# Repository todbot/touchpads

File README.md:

# Touchpads and Touchwheels

Some capacitive sense touch sensors: buttons and touchwheels

Design your own sliders and wheels with the
[Captouch Designer](https://todbot.github.io/touchpads/captouch-designer/)
web app (source in [`captouch-designer/`](./captouch-designer/)).

## Touchpads

Touchpads are capacitive sensing button inputs that consist of a copper
pad and (usually) 1M pull-down resistor, both hooked up to a microcontroller GPIO pin.
Code on a microcontroller repeatedly charges and times the discharge rate of the pad.
The discharge time changes when a finger is close to the pad. 
This change can be used to detect a button press. 
The CircuitPython [`touchio`](https://circuitpython-github-jepler.readthedocs.io/en/latest/shared-bindings/touchio/index.html) library and the Arduino library [`TouchyTouch`](https://github.com/todbot/TouchyTouch)
are two ways of using these capacative touch pads

### Touchpad boards

* buttons4x0 - Four 11 mm capacitive touch buttons for use with breadboards or in a project
  
  https://github.com/user-attachments/assets/d40d3ede-4ee4-4309-8d3a-04f324b11f05

## Touchwheels

These work by using only three capactive touch pads in a specific interleaved 
geometry and measuring the relative ratio of analog capacitive touch values 
between the pads to compute a distance along the slider. 

### Touchwheel boards made so far:

* TouchWheelSAO -- [Touchwheel SAO as part of  Hackaday Supercon 2024 badge](https://github.com/todbot/TouchwheelSAO)

* touchwheel0 - [available on Tindie as a kit!](https://www.tindie.com/products/todbot/touchwheel0-capacitive-touch-wheel/)

  Similar to an iPod's wheel, `touchwheel0` is a 30 mm (0.6") diameter 
  [rotary capacitive touch slider](https://onlinedocs.microchip.com/pr/GUID-A8A0085D-58D1-4E41-A07D-B93BFDE11AFE-en-US-4/index.html?GUID-FB5E9311-C731-4326-82D2-CD5F0ED8E378) that can be used with most any microcontroller. It uses three digital GPIO pins and requires no extra components. The included examples in CircuitPython and Arduino show how to turn the raw capacitive touch readings of the three pins into a linear 0-360º angle measurement.

* picoslidertoy - Available at the [picoslidertoy repo](https://github.com/todbot/picoslidertoy)

### Touchwheel Demos:

There are several examples on how to use the touchwheel:

- [demo0](./circuitpython/demo0/code.py) -
    CircuitPython example showing basic concept on touchwheel0
  
- [touchwheel_badgedemo](./circuitpython/touchwheel_badgedemo/code.py) - 
    CircuitPython example for the Hackaday SuperCon 2023 badge (where touchwheel0 PCBs were given away)
    
- [demo_dual](./circuitpython/demo_dual/code.py) - 
    CircuitPython example show two touchwheel0s in use

- more demos coming!

### What's in Tindie touchwheel0 kit: 

The [touchwheel0 kit](https://www.tindie.com/products/todbot/touchwheel0-capacitive-touch-wheel/)
on Tindie comes with:

- touchwheel0 black PCB
- 4 x 1M 0805 SMD resistors (only three needed, one is a spare)
- 1 x 4-pin pin header 

It makes a pretty good "first SMD soldering" exercise as the 0805 resistors 
are relatively big and not very heat sensitive. 

### Demo videos:

- demo dual:
  [(click to view on youtube)](https://www.youtube.com/watch?v=Db7S75eE-G8)

- demo0: 

  https://github.com/todbot/touchwheels/assets/274093/fc2b794f-5dff-42b4-8942-f141de19e4ab

## Useful links:

- [AN2934 - Capacitive Touch Sensor Design Guide (pdf)](https://ww1.microchip.com/downloads/en/Appnotes/Capacitive-Touch-Sensor-Design-Guide-DS00002934-B.pdf)
- [QTAN007 - Buttons, Sliders and Wheels - Sensor Design Guide (pdf)](https://www.mouser.com/pdfDocs/QTouch_QTAN0079.pdf)
- [AT02259: QTouch Schematic and Layout Checklist (pdf)](http://ww1.microchip.com/downloads/en/appnotes/atmel-42094-qtouch-schematic-and-layout-checklist_applicationnote_at02259.pdf)
- [SLAA891B: Automating Capacitive Touch Sensor PCB layouts with OpenSCAD Ti AppNote (pdf)](https://www.ti.com/lit/an/slaa891b/slaa891b.pdf?ts=1725369981627)
- [slider generator](https://cooltech.zone/tangara/labs/touchwheel-electrode-tool/)

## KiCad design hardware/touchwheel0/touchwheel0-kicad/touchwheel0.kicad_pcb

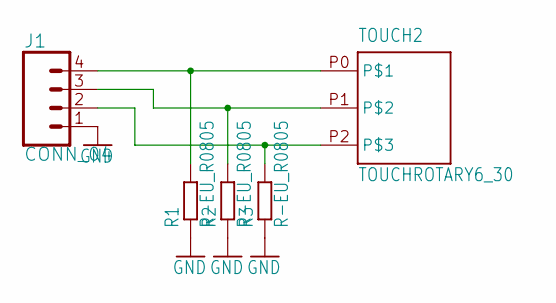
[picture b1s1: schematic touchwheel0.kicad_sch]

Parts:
J1: CONN_04; 1X04
R1, R2, R3: R-EU_R0805; R0805
TOUCH2: TOUCHROTARY6_30; TOUCHROTARY1B

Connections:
GND: J1.1, R1.1, R2.1, R3.1
unnamed: J1.4, R1.2, TOUCH2.P0
unnamed: J1.3, R2.2, TOUCH2.P1
unnamed: J1.2, R3.2, TOUCH2.P2

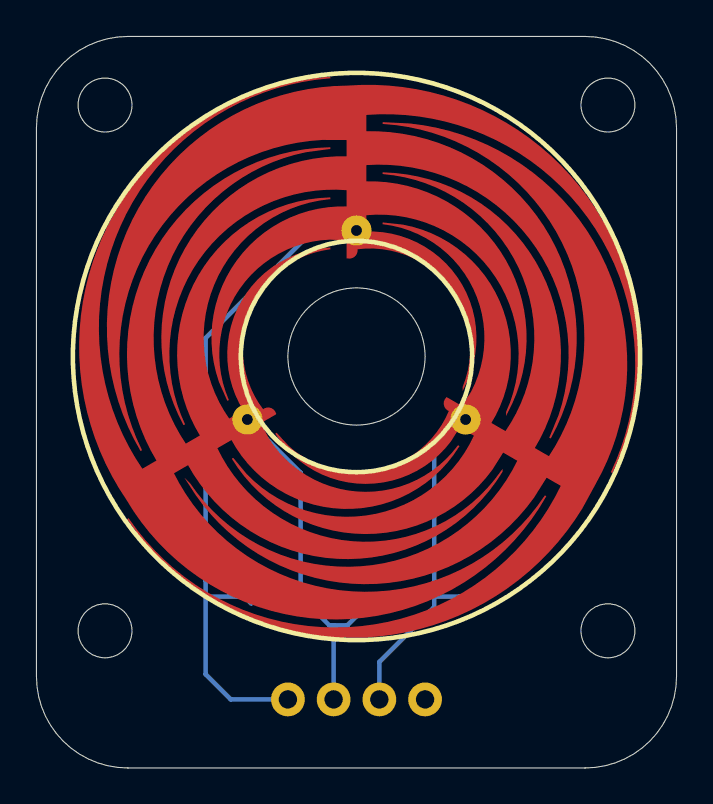
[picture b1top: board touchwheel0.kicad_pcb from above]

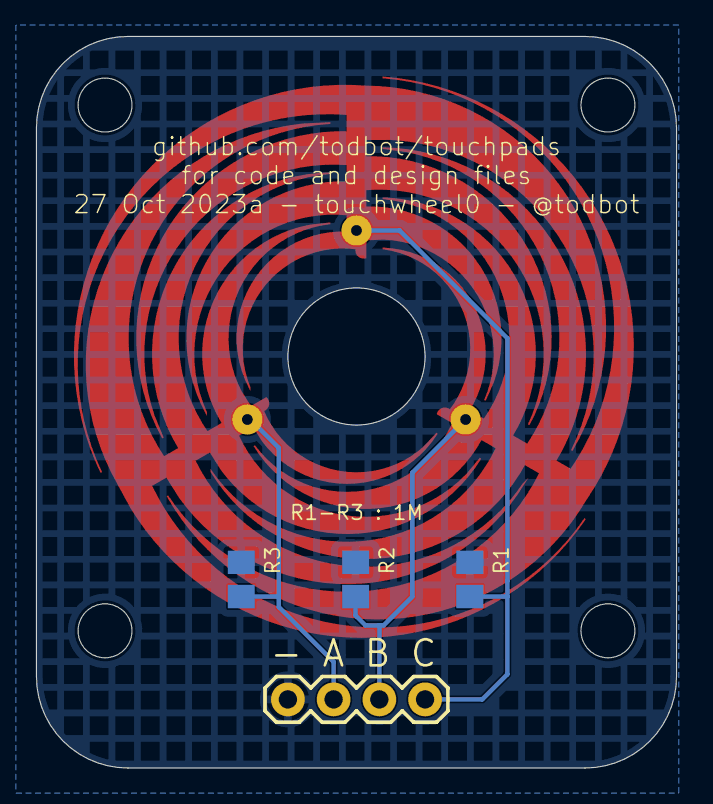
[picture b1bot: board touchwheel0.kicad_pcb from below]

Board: 2 copper layers, 35.6 x 40.6 mm, 9 parts (4 on the bottom side), 4 nets.

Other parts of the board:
UNK_HOLE_0: dummyfp0
UNK_HOLE_1: dummyfp1
UNK_HOLE_2: dummyfp2
UNK_HOLE_3: dummyfp3

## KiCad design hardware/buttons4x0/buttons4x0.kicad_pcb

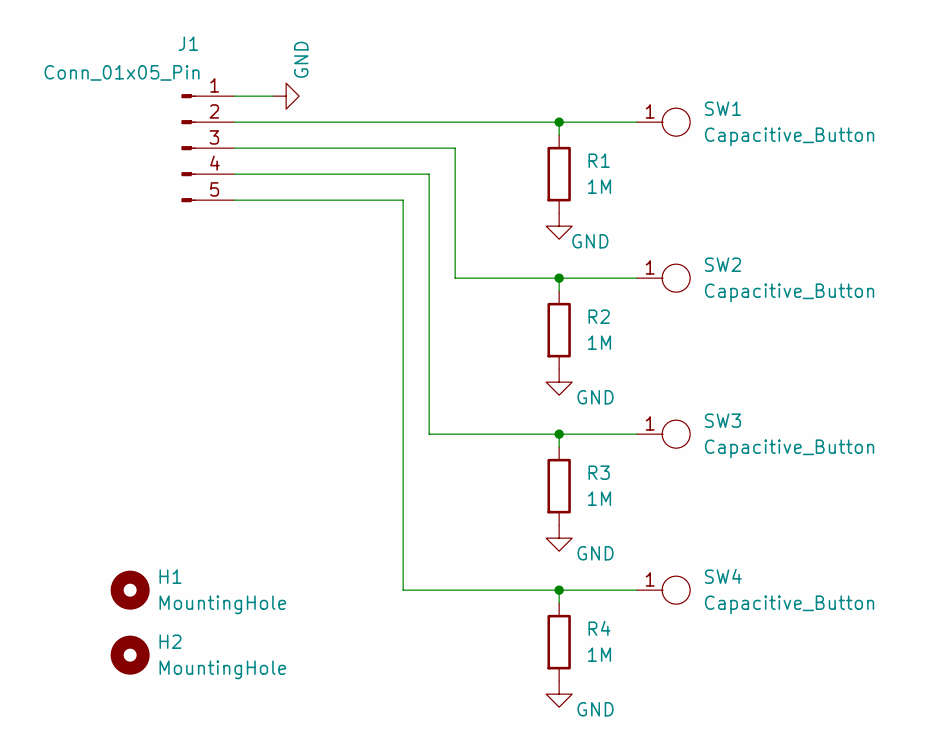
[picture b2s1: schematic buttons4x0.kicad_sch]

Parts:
H1, H2: MountingHole; MountingHole_2.7mm_M2.5
J1: Conn_01x05_Pin; PinHeader_1x05_P2.54mm_Vertical
R1, R2, R3, R4: 1M; R_0805_2012Metric
SW1, SW2, SW3, SW4: Capacitive_Button; Pad-CapTouch-11_2mm-roundrect

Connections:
GND: J1.1, R1.2, R2.2, R3.2, R4.2
unnamed: J1.2, R1.1, SW1.1 (A)
unnamed: J1.3, R2.1, SW2.1 (A)
unnamed: J1.4, R3.1, SW3.1 (A)
unnamed: J1.5, R4.1, SW4.1 (A)

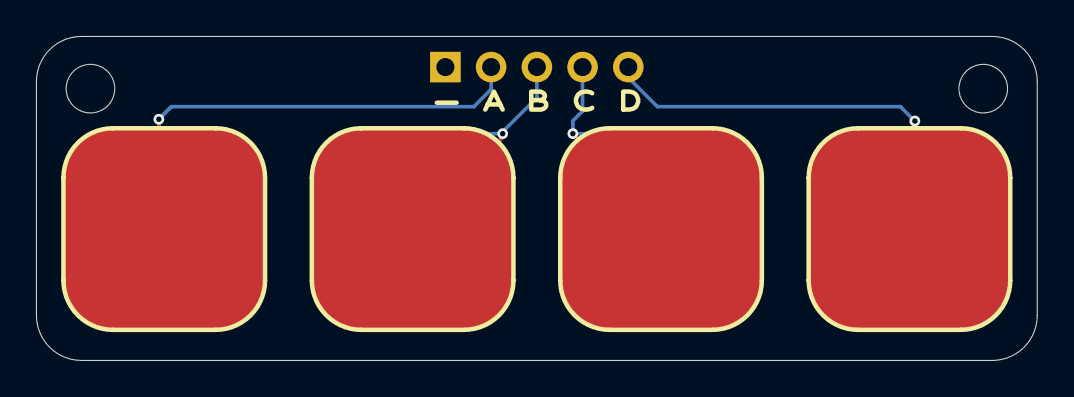
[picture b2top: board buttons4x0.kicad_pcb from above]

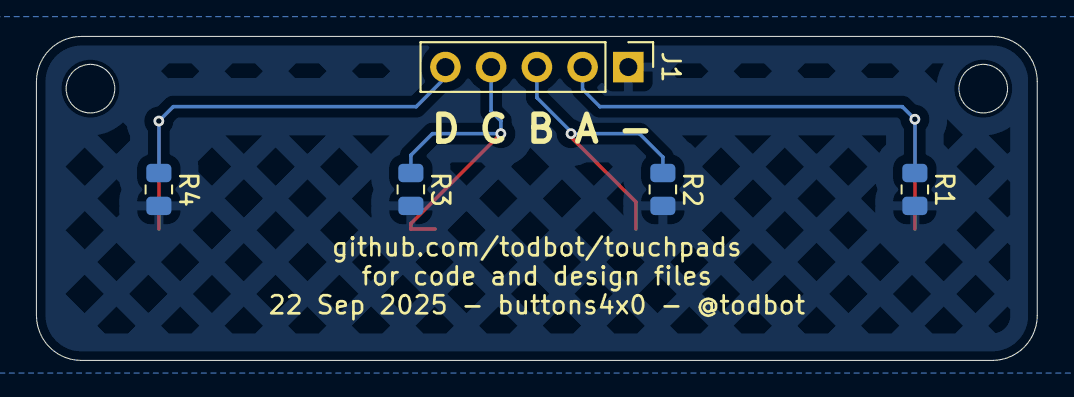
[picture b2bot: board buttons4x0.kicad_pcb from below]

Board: 2 copper layers, 55.6 x 18.0 mm, 11 parts (5 on the bottom side), 5 nets.

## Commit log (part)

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2025-09-22 update readme after rename from touchwheels to touchpads
2025-09-22 add buttons4x0
2025-09-22 remove old
2025-09-22 fix spacing to allow tiling a bit better
2025-09-22 add buttons4x0 docs
2025-09-22 before production
2025-09-23 readme update
2025-09-24 reorg and add buttons4x0 demo0
2025-09-29 buttons4x0 demo code tune
2025-09-29 Update README with GitHub asset link
    Added a link to GitHub asset for buttons4x0.
